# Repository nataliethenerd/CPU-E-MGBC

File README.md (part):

# Game Boy Pocket Color CPU E ONLY

Just incase you havent read it already, this is CPU E ONLY!!!!! CGB CPU E!

This board was adapted to CPU E by me, Natalie the Nerd. 
The CGB CPU E has a different pinout to the other varients of the CGB CPUs, I have documented the pinout via the board scans I created [here](https://github.com/nataliethenerd/boardscans/tree/main/CGB-CPU-06)

As a KiCad user, these boards were ported from Bucket Mouse's original Eagle files to KiCad using KiCad's built in converter. I cleaned them up and added the changes.

### MGBC CPU differences

The only differences is there is an added 2.5V LDO (NCP161ASN250T1G) and a couple more capacitors and no RAM. Here's the [iBom](https://nataliethenerd.github.io/mgbc-cpue.html)

Now onto the Mouse's original excellent documentation 

# Game Boy Pocket Color

My <a href="https://github.com/MouseBiteLabs/Game-Boy-DMG-Color">DMGC project</a> put a Game Boy Color put into an original Game Boy shell. But then I said, "Hey! This is neat, but I would rather it be small and cramped and have shorter battery life!" Enter the MGBC, or Pocket Color - a Game Boy Pocket (model name MGB) with the guts of a Game Boy Color (GBC). The PCB here is an original creation with some new features, though the concept and implementation of the "MGBC" or "Pocket Color" has been around for a while! Here are the project goals:

- A Game Boy Pocket aesthetic, using the original Game Boy Pocket shell and interfaces (link port, volume wheel, power switch, etc.), but with the capability of playing both Game Boy and Game Boy Color games.
- A nice, large IPS screen – the GBC Q5 XL IPS Backlight with OSD kit – with brightness and color palette control via the "navigation switch" housed where the contrast wheel used to be. (I will refer to the PCB attached to the Q5 screen as the “Q5 board”)
- A modernized, efficient switch mode power supply that can run off 2x AAA batteries or input from the DC jack, just like the original MGB. Testing shows that playing with NiMH AAA batteries can yield about 3.5 hours of gameplay at normal settings.
- Louder, cleaner sound through a modern audio amplifier.
- The option for tactile switches for the face buttons - like the GBA SP.
- No major externally viewable case modifications, to keep the OEM look and feel, outside of the screen, as much as possible.

All gerbers and source files can be found in this repo, as this project is fully open source. These PCB files and notes about the board, including customizations **and some troubleshooting tips**, can be found in the <a href="https://github.com/MouseBiteLabs/Game-Boy-Pocket-Color/tree/main/MGBC%20PCB#cpu-pin-functions">PCB folder</a>. Technical documentation of the board can be found in the <a href="https://github.com/MouseBiteLabs/Game-Boy-Pocket-Color/tree/main/Technical">Technical folder</a>.

**Do you want to make one?** Then you NEED TO READ this entire page. Seriously. Before asking a question, please review the <a href="https://github.com/MouseBiteLabs/Game-Boy-Pocket-Color#frequently-asked-questions">FAQ</a> at the bottom of the README for answers to.... frequently asked questions. Please try to find your answer in this repository - 95% of the time someone asks me something it's answered here already.

## Disclaimer

Before I go any further, please read this VERY important disclaimer, **IN IT'S ENTIRETY,** if you are thinking about making this yourself. **Don't let this picture happen to you!**

I made this project first and foremost for my own purposes. Nearly all of the features I have included are things I personally wanted. I have tried my hardest to make the project modular, if others would like to improve or change things easily, and I have also tried very hard to make the design somewhat less prone to potential errors during assembly. But in the end, every decision I made was for what I wanted the final product to be, with my skill level in mind.

So if you choose to build this project yourself, be warned - this is a considerably advanced, and expensive build. You must be comfortable with the fact that you may lose or damage expensive components. You are 100% liable for any damage done to your property or yourself. I am not responsible for any damage or loss of property incurred while attempting this project, or after completion of the project - you alone accept all risk. If you're *at all* questioning wether or not you can successfully attempt this project, please first practice with the <a href="https://github.com/MouseBiteLabs/Pocket-Mouse-Power-Board">Pocket Mouse Power Board</a> - this requires no original Game Boy parts, and the total parts cost of the board is less than $10. And before you dismantle a Game Boy, solder the FFC connector on the top of the MGBC board to make sure you are comfortable with long rows of fine pitch pins, as it is the same pin pitch as the much more expensive and important CPU. **If you have any difficulty assembling either the power board or the FFC connector, I highly discourage attempting the rest of the build.**

Furthermore, while I am confident in this design, I cannot claim full compatibility with every system configuration. **Especially if you decide to add a lithium-ion battery.** And there may be latent issues that have yet to crop up. If you see anything I may have missed, or some dubious design choice, feel free to ask questions or comment as such - feedback is appreciated, corrections are welcome.

In summation: **DO NOT attempt this project if you are uncomfortable or inexperienced with detailed electronics troubleshooting, or are not proficient in soldering! This is in NO WAY a beginner's project. You will AT MINIMUM need to be proficient in <a href="https://youtu.be/5uiroWBkdFY?t=110">drag soldering</a> and <a href="https://youtu.be/X3Rc1s6EpSI">hot air reflowing</a>. If you have not gained proficiency in these soldering skills, DO NOT ATTEMPT THIS PROJECT. You accept all risks and costs associated to this build if you choose to attempt it.**

(These parts are *tiny*. Quarter for scale - do not install a quarter in your final build.)

## Bill of Materials (BOM)

There are a handful of categories for the parts you need for this build. Please review all of them! The total BOM cost will come out to anywhere between $100 and $200 (NOT including the cost of a donor Game Boy Color console!) depending on the options you choose, which OEM parts you re-use, and any potential deals you can get on certain parts. Note that with the exception of a few components from a donor Game Boy Color, *most* of the electronic parts are brand new.

### I. Circuit Boards
  
First and foremost, you will need two brand new circuit boards for this build:
- <a href="https://github.com/MouseBiteLabs/Game-Boy-Pocket-Color/tree/main/MGBC%20PCB#mgbc-mbl-01">the main MGBC circuit board</a>, and 
- a power supply board that fits in the U5 socket on the MGBC board (like my <a href="https://github.com/MouseBiteLabs/Pocket-Mouse-Power-Board">Pocket Mouse Power Board</a>)

Again, I sell <a href="https://mousebitelabs.etsy.com/listing/1459241814/game-boy-pocket-color-pcb-mgbc-mbl-01?utm_source=Copy&utm_medium=ListingManager&utm_campaign=Share&utm_term=so.lmsm&share_time=1694127166906">the MGBC board</a> and <a href="https://mousebitelabs.etsy.com/listing/1473483915/pocket-mouse-power-board?utm_source=Copy&utm_medium=ListingManager&utm_campaign=Share&utm_term=so.lmsm&share_time=1694127201480">my regulator board</a> on my Etsy store. You can alternatively use the files in the MGBC PCB folder to order it yourself. Please see the MGBC PCB folder for more info.

You can also use other power supply boards from other creators - check the <a href="https://github.com/MouseBiteLabs/Game-Boy-Pocket-Color#v-compatibility-with-other-mods">Compatibility</a> section below for more information. 

**I don't recommend using an original power board from a Game Boy!**

### Information on Older Revisions

The current revision is v2.1, but you may have an earlier board (if you bought one from me, rest assured it will work perfectly fine - most of the changes between for-sale revisions are inconsequential to the end user). The BOM has changed slightly for v1.6 and later boards, compared to previous revisions. Please view the Excel and/or .csv file above for BOM information (or contact me). Here's a short list of information about the older boards, and what is required/recommended when using them:

| Revision | Recommendations |
| ---- | ---------------------------------------------------------------------------------------------------------------------------- |
| v1.0 | You are a masochist. You're on your own for this one.                                                                        |
| v1.1 | Are you me? No? Then did you rob my house?                                                                                   |
| v1.2 | You're one of the beloved beta testers. You didn't build it yet? For shame. Contact me.                                      |
| v1.3 | These should be practice boards only.                                                                                        |
| v1.4 | Use tactile buttons. Minor shell trimming may be required for volume dial and rocker switch.                                 |
| v1.5 | Minor shell trimming may be required for volume dial and rocker switch.                                                      |
| v1.6 | No important differences compared to the latest revision, but check EM7 and DC/BT+ requirements!                             |
| v2.0 | No important differences compared to the latest revision.                                                                    |

### II. Brand New Electronic Parts

The MGBC board uses mostly all-new components. This is not a direct-transfer board. The master BOM with every electronic component required for the main MGBC circuit board is provided in the folder in Excel format. Note that some parts may be out of stock at the links provided, but many can be found at alternate other retailers online, or have a proper substitute. Here is a saved cart from Mouser that contains all the parts in the BOM Excel, including some duplicates: https://www.mouser.com/ProjectManager/ProjectDetail.aspx?AccessID=854e7f6cf9

*Note: This cart link is for v1.6, v2.0, and v2.1 boards. Please check out the BOM Excel or .csv file above for information about v1.5 and earlier.*

Double check to see if any parts are missing, and consider ordering multiples of some parts. Also, there are some parts you may want to remove (like the tactile switches). **If a part is backordered, or out of stock** - check the Excel file, or the BOM listed at the bottom of the MGBC PCB folder. There may be alternate part options listed. You can also check for stock at places like Digikey, Newark, or LCSC. And you can always use Octopart.com to help find in-stock parts at other websites. Please understand that I can't maintain the cart for every out-of-stock part, so please do some research :)

Also note, while I do recommend the board, this BOM does not include parts for the Pocket Mouse Power Board. <a href="https://github.com/MouseBiteLabs/Pocket-Mouse-Power-Board">Please review my github on that board</a> for more information if you wish to use it for your power supply!

### III. Game Boy Electronic Parts

*Despite this being a **Pocket** Color, you don't actually need a Game Boy Pocket. However, this project **does require** at minimum a Game Boy Color.*

There are a handful of parts that I have not located aftermarket substitutes for, and will therefore necessitate an original Game Boy console to salvage from. Please note that removing these parts is not a trivial task, and **requires advanced soldering and desoldering skills to be successful.**

The following parts are required from an original Game Boy Color console:

  -	U1 – CGB CPU (all revisions *except* REV E, which is *incompatible*)
  - X1 – 8.388 MHz crystal oscillator

The following parts are required from an original Game Boy Color **OR** Game Boy Pocket console:

  -	P1 – Cartridge connector
  -	P5 – Headphone jack

The following parts can be salvaged from a Game Boy Color, but newly manufactured commercial off-the-shelf options exist:

  - U2 – LH52256CVTXIZ (SRAM); alternate: https://mou.sr/3f8G0Mi
  - EM10 – input filter; alternate: https://mou.sr/3FiMvXw

The following parts can be salvaged from a Game Boy Color *or* Game Boy Pocket, but aftermarket options exist:

  -	VR1 – Volume dial
  -	SW1 – Power switch
  -	P3 – Link port
  -	P4 – DC jack

### IV. External Build Parts

The following is the high-level BOM - basically, the Game Boy part. Note that parts that deviate from the ones listed here (like different shell designs) might necessitate different fitment modifications, or end up being incompatible. Note that this list is not a comprehensive list of all the places you can get these parts. I encourage you to search around if you can't find what you want here. 

-	**Shell:** I generally recommend the Funnyplaying "IPS Ready" ones if you don't want to trim anything. If you don't use these, then you're on your own for how to prepare it - generally, you can follow guides for preparing a Pocket for an IPS screen kit.
    - RGRS: <a href="https://retrogamerepairshop.com/products/funnyplaying-game-boy-pocket-q5-ips-ready-shell-housing-no-cut?pr_prod_strat=copurchase&pr_rec_id=d8b0186ad&pr_rec_pid=6280907751596&pr_ref_pid=6115075391660&pr_seq=uniform">FunnyPlaying Game Boy Pocket IPS Backlight Ready Shell Housing No Cut</a>
    - FunnyPlaying: <a href="https://funnyplaying.com/collections/product/products/gbp-retro-pixel-ips-coustom-shell?variant=33054643060797">GBP RETRO PIXEL IPS CUSTOM SHELL</a>
-	**Screen Kit:** This is the important one. You need this specific type of kit - the Q5 IPS with OSD. It goes by many names, the maker is Hispeedido (*not* FunnyPlaying). Kits that have the screen laminated to a GBC lens are *not* compatible, but kits that include a lit-up logo on the bottom part of the screen are fine to use. Make sure you DO NOT get the Game Boy Pocket version - it is not compatible! Also, be sure to test this screen kit before installing it, preferrably with an original Game Boy Color. Sometimes they arrive damaged, and once you've installed, it may not be possible to get a refund.
    - RGRS: <a href="https://retrogamerepairshop.com/products/game-boy-color-q5-ips-backlight-with-osd?variant=37646279213228">GBC Q5 XL IPS Backlight with OSD</a> OR <a href="https://retrogamerepairshop.com/collections/gbc-displays/products/game-boy-color-q5-osd-ips-kit-with-color-changing-logo?variant=41819042185388">Game Boy Color Q5 OSD IPS Kit with Color Changing Logo 
    - AliExpress: <a href="https://www.aliexpress.us/item/3256801650459088.html?spm=a2g0o.productlist.main.1.758e53f17WUFK2&algo_pvid=24ef67e3-d608-4269-a663-05eafed1bd17&algo_exp_id=24ef67e3-d608-4269-a663-05eafed1bd17-0&pdp_npi=3%40dis%21USD%2145.9%2145.9%21%21%21%21%21%4021224e9b16816641208271256d074d%2112000017802039303%21sea%21US%210&curPageLogUid=dCymHIE0cr4X">GBC Q5 IPS LCD Kit</a>
    - HHL: <a href="https://handheldlegend.com/products/game-boy-color-ips-lcd-q5-hispeedido">Game Boy Color IPS LCD Q5 - Hispeedido</a>
I have not thoroughly tested it, but the CGS (Cloud Game Store) display should be electrically compatible as of v2.0. It will need some kind of method of centering the image if you choose to use it, though. (At the time of writing, I have heard there is a seller on Taobao selling laminated CGS kits...)
  -	**Lens:** I recommend you get an "IPS Lens" as the viewing area is slightly larger than the OEM one. 
    - RGRS: <a href="https://retrogamerepairshop.com/collections/gbp-lenses-1/products/funnyplaying-game-boy-pocket-ips-retro-pixel-mod-led-hole-glass-screen-lens?variant=37635319988396">FunnyPlaying Game Boy Pocket IPS Retro Pixel Mod LED Hole Glass Screen Lens</a>
    - FunnyPlaying: <a href="https://funnyplaying.com/products/gbp-retro-pixel-ips-glass-lens?_pos=1&_sid=ec7345577&_ss=r&variant=31969857437757">GBP RETRO PIXEL IPS GLASS LENS</a>
- **Buttons:** Funnyplaying models are generally OEM-like (IMO), but you can also use OEM ones. Or any other maker of buttons! (Make sure you get Game Boy *Pocket* buttons - Game Boy *Color* buttons will not fit.)
  - RGRS: <a href="https://retrogamerepairshop.com/collections/gbp-buttons-1/products/funnyplaying-game-boy-custom-pocket-buttons?variant=41432879169708">FunnyPlaying Game Boy Pocket Custom Buttons</a>
  - LabFifteen: <a href="https://labfifteenco.com/collections/game-boy-pocket-buttons">Custom buttons</a>
  - FunnyPlaying: <a href="https://funnyplaying.com/products/gbp-custom-buttons?_pos=2&_sid=1bdf0ccb6&_ss=r&variant=33054652039229">GBP CUSTOM BUTTONS</a>
- **Membranes:** Important, but very forgettable! You will need them even if you install tactile switches.
  - RGRS: <a href="https://retrogamerepairshop.com/collections/gbp-buttons-1/products/funnyplaying-game-boy-pocket-silicone-button-contact-pad-membranes?variant=40593166401708">FunnyPlaying Game Boy Pocket Silicone Button Contact Pad Membranes
  - FunnyPlaying: <a href="https://funnyplaying.com/products/replacement-silicone-pads-for-gbp-mgb?_pos=3&_sid=1bdf0ccb6&_ss=r&variant=39378004705341">GBP/MGB REPLACEMENT SILICONE PADS</a>
- **Speaker:** There are tons of options for this as well, including using the OEM one. Game Boy Color *and* Game Boy Pocket speakers are compatible, since they are the same part.
  - RGRS: <a href="https://retrogamerepairshop.com/collections/gbp-audio/products/funnyplaying-clear-game-boy-color-speaker?variant=37728953761964">FunnyPlaying Clear Game Boy Color & Pocket Speaker</a>
  - FunnyPlaying: <a href="https://funnyplaying.com/products/clear-gbc-mgb-speaker?_pos=1&_sid=2cc6157b6&_ss=r">CLEAR GBC/MGB SPEAKER</a>
- **Battery Tabs:** This one is another part I commonly forget about. You *cannot* use Game Boy Color ones, you *must* use Game Boy Pocket battery terminals. Luckily, they're very easy to find.
  - RGRS: <a href="https://retrogamerepairshop.com/collections/gbp-power/products/gbp-game-boy-pocket-high-quality-replacement-battery-contact-terminals?variant=37893131305132">GBP Game Boy Pocket High Quality Replacement Battery Contact Terminals
- **Stickers:** Completely optional, but they can really bring a build together. Especially if you have custom Pocket Color stickers!
  - Nextstopplease: <a href="https://nextstopplease.square.site/product/gb-pocket-color-label/196?cp=true&sa=true&sbp=false&q=false">GB Pocket Color Label</a>
  - 8bitlabels: <a href="https://www.etsy.com/shop/8bitlabels?ref=simple-shop-header-name&listing_id=1097537372">8bitlabels on Etsy</a>

<b>Buying from RGRS? Consider helping out some cool people with these referral links:</b>
- <a href="https://retrogamerepairshop.com/?ref=ltyD2rUX">CodyWick</a>
- <a href="https://retrogamerepairshop.com/?ref=HSj4v5OO">JackV</a>

<b>Or use one of these other discount codes at checkout:</b>
- Nataliethenerd
- B23N
- Tito

### V. Battery Selection

I developed this system almost exclusively with rechargeable eneloop Pro NiMH AAA batteries. After finishing up development, I tried out regular alkaline AAAs. What I found, and some others have found, is that they are less reliable to use than NiMH batteries, particularly during start-up. When using alkaline batteries, after they have been discharged for an hour or two, sometimes the screen and power LED will flicker for a bit before fully coming on. This also varies between brands - I found Energizer Max batteries to perform much better than Duracell Coppertop batteries, for example. Duracells caused much more stuttering during the start-up sequence. Other brands or types may perform better, but I'm not about to buy a bunch of disposable alkalines to find out which.

However, the rechargeable NiMH AAA batteries I tested *do not* have any of these issues. And I tested these a lot during development, at many different states of charge. They are seemingly better suited for power delivery, and I never experience any kind of stuttering during start-up. I believe this is due to the generally higher internal resistance of alkaline batteries (a quick sampling of popular battery brands show approximately 50 mOhms internal resistance for NiMH chemistry, but 150+ mOhms internal resistance for alkaline chemistry). 

Rechargeable NiMH batteries give you about 3 to 6 hours of gameplay based on your settings and game selection, and as long as you have more than one set, you can easily charge one set while you play with another set. <A href="https://www.amazon.com/Panasonic-BK-4HCCA8BA-eneloop-Pre-Charged-Rechargeable/dp/B00JHKSL0A/ref=sr_1_1_pp?keywords=eneloop%2BAAA&qid=1690853200&sr=8-1&th=1">Here's a listing for the eneloop pro batteries I use in all of my Game Boys.</a> Other brands of rechargeable batteries I have seen used are Ikea LADDA batteries, and Jugee batteries.

#### Lithium Ion Batteries

Lithium-ion batteries (or LiPos) are another option, but I do not fully detail how to use them in this repository. You must be knowledgeable enough on your own to utilize them. Please review the entire repo for crucial information if you *do* decide to go with a LiPo.

I have created <a href="https://github.com/MouseBiteLabs/Pocket-Protector-Power-Board">my own LiPo board</a> to fit in the U5 socket, but I really recommend using AAAs. It will make the assembly easier and safer.

Nataliethenerd's <a href="https://www.nataliethenerd.com/product-page/safer-charge-dc">Safer Charge DC</a> board is also compatible with the MGBC. Instructions for how to use it is in the Testing and Assembly section.
  
### VI. Compatibility with Other Mods

You don't need any extra mods to complete the MGBC build, but there are some options available. One of the goals for the MGBC was to provide compatibility with various mods by other makers. In general, I tried to make the board similar to the Game Boy Pocket PCB in terms of solder points for different kinds of mods. The MGBC will not benefit from any mods that include audio amplification/"cleaning" or tactile button mods, as I've included those improvements already. Check out the <a href="https://github.com/MouseBiteLabs/Game-Boy-Pocket-Color/tree/main/MGBC%20PCB#customization-options">Customization Options</a> section in the MGBC PCB folder for information on those.
  
Here are a sample of my favorite mods for the MGBC:

  - <a href="https://www.etsy.com/listing/1348046388/game-boy-pocket-battery-indicator-mod">Leggomyfroggo's Two-Stage Battery Indicator Mod</a>: goes in place of the power LED, changes color when battery gets low
  - <a href="https://www.etsy.com/listing/1422095615/frogulator-game-boy-colorpocket-dc">Leggomyfroggo's Frogulator</a>: a power supply that slots into the U5 socket; eyes light up for battery power indication
  - <a href="https://www.muramasaentertainment.com/product/pocket-power-pocket/">Muramasa's Pocket-Power Pocket</a>: an all-in-one LiPo charger including USB-C port; requires some shell cuts and **removal of EM7 for v1.6 and earlier** [untested]
  - <a href="https://github.com/marshallh/gbpp">marshallh's Game Boy Pocket Power</a>: a power supply that slots into the U5 socket; has LiPo support (solder wires through the DC and BT+ holes on the MGBC board, and **remove EM7 on v1.6 and earlier** - requires USB-C board for charging and some shell cuts [untested]
  - <a href="https://github.com/skimzor/SZ-REG">skimzor's SZ Regulator</a>: a power supply that slots into the U5 socket; customizable print on the front of the board through <a href="https://ko-fi.com/skimzor">skimzor's Ko-Fi page</a>
  - <a href="https://www.nataliethenerd.com/product-page/gbp-led-boards">Natalie the Nerd's LED Boards</a>: button LED backlight board

Important note for using external mods: you must be aware that the voltage on the SW net (the output of the power switch, connected to pin 1 on the power board socket) will remain connected to the batteries as long as the power switch is on. If your mod connects to the power switch output, then be aware there *will* be a condition where the 5 V on-board is at zero volts, and the battery voltage will still be above 2 V. This may cause issues, such as power draw through resistors even when the power is off, or leakage through protection diodes in certain devices. Please use accordingly.

## Testing and Assembly

I'm going to split this into a few separate sections. This is the general process I follow when assembling an MGBC.

### Circuit Board Assembly

Usually when I'm populating a board, I follow this order:
  
1) Assemble all the non-Gameboy surface mount components first, not including P2, U2, C24, C29, and C45. 
  
2) After soldering these components, I solder the CPU and RAM in, then the FFC connector.
  
3) I use hot air and solder paste to reflow X1, C24, C29, and C45 onto the board. Be sure to either cover the FFC connector with kapton tape to avoid melting the plastic, or heat the board from the bottom.
 
If the build is going to utilize tactile buttons (the ones that are clicky, like on the GBA SP) I install *at least* the start and select ones now. After the headphone jack and DC jack are in, it's tricky to get the start and select tactiles in.
  
4) Finally, I add most of the other external-facing components - VR1, P3, P4, P5, SW1, SW2, D2, the speaker, and the battery terminals. The only parts that I don't populate at this point are the cartridge connector (P1) and the power board (U5). 

**NOTE 1** - Keep VR1 and SW2 as far inside the board as the holes allow. This will reduce interference with the shell. You may need to file away a bit of the shell in order for the knobs to turn freely. It may be a good idea to do a quick fitment test in the shell before going farther into assembly.

**NOTE 2** - You may have to trim the pins on VR1, the volume dial, before soldering. I cut them down in half to make them fit nicer.

### Setting up for AAA vs LiPo

I generally recommend using NiMH AAAs in builds, because they are easier and safer to deal with, they can be swapped in quickly as opposed to waiting for the battery to charge up, and don't require any shell modifications to use (LiPos require a shell cut to fit a USB port, which isn't fun). The only thing you need to do if you're going to use AAAs, which the MGBC is set up for natively, is connect the two holes labelled BT+ and DC together with a wire or 0 ohm resistor. This is also only required on v2.0 and later boards - v1.6 and earlier do not require this. Shorting these holes together connects the DC jack to the input of the regulator. So if you forget to add it, then your DC jack won't work (which may or may not matter to you anyway). **DO NOT SHORT THESE TOGETHER IF USING A LITHIUM-ION BATTERY.**

If you really want to add LiPo support to your build, you're on your own for figuring out how to set it up. The important thing to note on the MGBC board is, for boards v1.6 and earlier, **DO NOT INCLDE EM7**. This component must be removed from the final build. Make absolutely sure you do this - failure to do so may damage your battery and/or system. In version 2.0, you must include EM7 on every build.

Also, to get the power LED to dim at the correct time, remove R6 from the main MGBC board.

If you're using Nataliethenerd's <a href="https://www.nataliethenerd.com/product-page/safer-charge-dc">Safer Charge DC</a>, connect a wire from the "To F1" pad on the back of the board to the BT+ hole on the MGBC, and a wire from the "To 5V" pad on the back of the board to the pad on the USB-C breakout board. Then install the board into the U5 socket as normal.

And, as a mandatory disclaimer, **LITHIUM-ION BATTERIES ARE DANGEROUS. USE AT YOUR OWN RISK. I AM NOT RESPONSIBLE FOR YOUR HOUSE BURNING DOWN. YOU ARE RESPONSIBLE FOR FIGURING OUT HOW TO USE A LIPO ON THIS BOARD.**

### Testing the Power Board and IPS Kit
  
The next step to test is the power board, or U5. If you are using my LiPo power board, the steps to test that board are detailed <a href="https://github.com/MouseBiteLabs/Pocket-Protector-Power-Board">in the repository.</a> I *highly* suggest making sure you've assembled the power board correctly before directly connecting it and powering it all on, cowboy style. If you're able to test your power board before installation, definitely do that, but if you're not sure how, or don't have the ability, then you can actually use your mostly-assembled MGBC board to test it. 
  
Solder wires on pins 1, 2, and 3 from the MGBC board to the power board (the left three holes of the power board). Don't connect the other side of four pins just yet - pin 7 is the 5 V pin, which powers the rest of the Game Boy. Keeping pin 7 depopulated, you can place the Game Boy in the back half of the shell to connect up batteries, or use a power supply clipped to the battery terminals. Turn the power switch on. Use a multimeter to measure the voltage from pin 7 (positive test probe) to GND (negative test probe). You should read approximately 5 V here - anything more than 5.1 V or less than 4.9 V means you've likely got something wrong on your power board.
  
(In this picture, the red circle is pin 7, the blue circle is pin 3, or GND - this is for illustrative purposes only, I recommend testing the board before fully mounting it to the MGBC board.)

If you confirm you have 5 V on pin 7, then remove the wires and connect the board via header pins (if not, check the next section for some troubleshooting advice). Finally, you'll want to test the screen kit. Slide the FFC cable into P2 on the MGBC board, and make sure the cable is all the way in and the bale is pushed all the way down. Let the screen hang over the front of the board. I recommend placing something insulative - like a piece of paper, or kapton tape - over the empty holes of the cart connector, to prevent the back of the display from shorting on the pins. If you have a power supply, you can use that to power it on the battery terminals (set it for 3 V, 1.5 A). If not, you can again put the Game Boy in the back half of a Game Boy Pocket shell to use batteries. (I have mixed results with using battery holders with alligator clips.)

Turn it on, and check for these things:
  
1) Power LED turns on
2) The speaker makes the start-up ding (use headphones to check both left and right channels, and check the volume)
3) The screen shows the GBC splash logo
  
Some quick troubleshooting tips - first, make sure the batteries are in all the way (or your power supply is set correctly) and the cable for the IPS kit is inserted fully and the bale is pushed all the way down. If only the LED isn't turning on, you might have the LED backwards. If you can hear the start-up noise, but nothing on the screen, then check the connections on the FFC connector and the top row of pins on the CPU - they probably need a reflow. If you get a blank screen, but no start-up jingle, then check the connections on the FFC, CPU, and RAM chips. And if you have the splash screen, but no audio, then check your speaker, headphone jack, and orientation of tantalum capacitors. If nothing is happening when you flip the switch, or you still cant figure out where your error is coming from, check out the <a href="https://github.com/MouseBiteLabs/Game-Boy-Pocket-Color#troubleshooting-common-electrical-issues">Troubleshooting</a> section for a few more detailed troubleshooting tips, and the <a href="https://github.com/MouseBiteLabs/Game-Boy-Pocket-Color/tree/main/MGBC%20PCB#cpu-pin-functions">CPU Pin Function diagram</a> in the PCB folder.

*Note: If you're using the Pocket Mouse Power Board, you may have to wait a few seconds after inserting batteries the first time before it will turn on with the power switch. Once the batteries have been in the system for a few seconds, it will act completely normally.*
  
Once you've verified the system boots up correctly, and you have acceptable sound coming out of the speakers and headphones with the start-up noise, you can go ahead and put the cart connector into the board. I save this for last, because there are a few components in the audio circuit close to the connector, and they're difficult to rework without melting the cart connector plastic.
  
When you install the cartridge connector, be sure to trim down the pins nearly flush to the PCB. Then, I usually cover the exposed solder with kapton tape. The Q5 screen sits right above these pins, and the back of it can short to the cart connector pins once the system is fully assembled.

You will also want to test out the cartridge connector! Put the screen back in, and power it up like you tested above, but with a game inserted this time. If you get a garbled Nintendo logo, or the game doesn't boot at all, make sure your cartridge and cartridge connector are cleaned. You may also want to reflow the cart connector or the bottom row of CPU pins in case one of those lines are not making proper connection.

I suggest running the color tests in the <a href="https://github.com/pinobatch/240p-test-mini/releases/">240p test suite ROM</a>, if you have a flash cart to run it on. It will tell you if you have any poor connections on the FFC lines - the screen might work, but you might be missing a connection on one of the 15 RGB pins! If your colors look off, reflow the connections on the top row of pins on the CPU and/or the FFC connector. This picture (provided by <a href="https://retrogamerepairshop.com/?ref=HSj4v5OO">JackV</a>) shows a before and after pic for reflowing a few mis-soldered color pins.

### Customization Options

There are a number of options you have to customize your build. This includes, among other things: adding a reset button, adding tactile switches for the buttons, and changing the brightness of the LED. Review the <a href="https://github.com/MouseBiteLabs/Game-Boy-Pocket-Color/tree/main/MGBC%20PCB#customization-options">Customization Options</a> section of the MGBC PCB folder for more information.

This is also the point where I would install any desired mods discussed above in the <a href="https://github.com/MouseBiteLabs/Game-Boy-Pocket-Color#v-compatibility-with-other-mods">Mod Compatibility</a> section (other than power boards, obviously). Though, there aren't too many mods out there that would be required to add. Again, there is absolutely no need for additional audio mods or power cleaner mods on this build.

### Troubleshooting Common Electrical Issues

I'm not going to delve into a lot of detail here, just some basic troubleshooting you can perform. Remember, this project is meant for those with experience in electronics assembly and troubleshooting, so you should be able to figure some of this out by yourself! These tips won't include simple things to check like "check for cold solder joints" or "make sure you have the right parts installed" and whatnot, but that doesn't mean that isn't your root cause!

**Issue: No power to U5 pins 1 or 2**

Are you getting voltage out of the batteries or DC jack? Measure the voltage across pin 2 of the U5 socket to GND - this should read whatever voltage your batteries or DC jack is outputting. Measuring the voltage from pin 1 of U5 to GND will give you the same result as pin 2 when the power switch is on, or zero volts when the power switch is off. 

If you get incorrect results, then check the following:
  - Make sure F1 or F2 are not blown. (Were you soldering when you had batteries installed? For shame!)
  - Check orientation of D1 - did you put it in backwards?
  - Check orientation of EM10 - is it 90 degrees rotated?
  - Check for a dirty DC jack (P4) - you should read nearly zero ohms with a resistance check across pins 2 and 3 when you don't have anything plugged in!
  - Make sure the batteries completely touch the battery terminals in the battery bay. This frequently happens to me in aftermarket shells without the battery separator.
  - Clean your power switch regardless of any issues (it will improve the switch action reliability), but if it's particularly dirty, you may not get any voltage reading on pin 1 even when it's turned on
  
**Issue: Severe power glitches during start-up; plugging in headphones sometimes resets system**
  
  - Make sure C8, C21, C26, and C27 are placed in the correct orientation. Remember, the stripe on tantalum capacitors indicates the POSITIVE side of the device.
  - Ensure R22/R23 are 1 kΩ resistors.
  - Clean your power switch properly.
  
**Issue: No sound or bad quality sound**

- Make sure C8, C21, C26, and C27 are placed in the correct orientation.
- Plug in headphones to check if the issue is related to the speaker or both speaker and headphones. If you get audio out of your headphones but not your speaker, then:
  - Check for continuity from pin 5 on the headphone jack (top right corner when viewing from below) to GND. When headphones are not plugged in, this pin should be connected to ground. If it isn't, clean your headphone jack, or get another.
  - Try another speaker, if you have one.
- If your issue is both speaker *AND* headphones, then:
  - Clean your volume dial by dripping IPA in it and spinning it back and forth. Consider replacing it with a new aftermarket version.
  - Reflow components in the audio circuit and/or the CPU audio pins.
  
**Issue: White screen, glitchy display, miscolored display, stuck on the boot logo**

- Make sure your screen ribbon cable is inserted all the way into P2 and the bale is pushed all the way down.
- Reflow the SRAM (U2) and make sure all pins are well-connected to the board.
- Reflow the FFC connector (P2) and make sure all pins are well-connected to the board.
- Reflow the CPU (U1) and make sure all pins are well-connected to the board.
- If miscolored, make sure the palette isn't being cycled on the IPS kit, as there is a touchpad that cycles through different color modes.
- If you're stuck on the boot screen *only* with a game inserted, check to make sure the cartridge and cartridge connector you're using is clean and making good contact.

### Final Assembly

Before assembling the board into the shell, it's a good idea to prepare the Q5 board solder pads. First, remove the touch sensor leads. Then cut six 30 gauge wire segments and solder them on the brightness, palette, battery, and OSD input pads. You do not need to solder a wire to the GND pad. The one connected to the brightness touch sensor pad will be longer than the others, as it has to cut over to the other side of the board. These wires will be soldered to the top of the board after the screen is installed.

Then, put the lens on the front half of the shell, take the screen protector off of the IPS screen, and carefully place it in the back half of the shell - be sure no dust or hair is between the lens and the screen! Then place the buttons and membranes down.

**Note: Be extremely careful with the screen. It is fragile. If you break it, you can sometimes buy one separately. They're just screens that were used in Blackberry Q5 phones.**
  
Next is to put the assembled PCB into the shell. Remember that you may need to lightly file away part of the shell around VR1 (volume dial) and/or SW2 (rocker switch) if the knobs interfere with the shell. Put screws down into the proper holes, and feed the IPS kit cable into P2 and secure the bale. The cable is a bit stiff so be careful installing it. Also at this point, *very carefully* solder the six wires from the IPS kit onto the main MGBC PCB. **Be extremely cautious not to melt any plastic on the shell!** Though if you're attempting this mod, I would hope you have a steady enough hand to keep the soldering iron away from the melty bits ;)

Then all that's left is to put the power switch in its holder, and secure the back half of the shell on. Well, and center the image. It's going to be offset a bit. That's where the Q5 kit's image-centering functionality comes into play. Open the menu by pressing Select, A, and B at the same time. Navigate up and down in the menu with A and B respectively, and hold select and press A to select the screen offset options (select+A again confirms your change, select+B backs out of it). Adjust the V (and maybe H) coordinates so that the image is centered, for my build this was about 46 vertical, 37 horizontal.

*Also, if your screen kit includes the option for a backlit Game Boy Color lens logo, be sure to disable that in the OSD menu. On the left picture you can see the blue bar at the bottom, that's the backlit logo option before disabling it.*

Add any stickers you want, and the MGBC is complete!

## Auxilliary Controls
### Q5 XL IPS Backlight with OSD
-	Select + A + B: Open the OSD menu
-	Select + A: Enter
-	Select + B: Exit
-	A: Increase
-	B: Decrease

### Navigation Switch
-	Rock up: Advance screen brightness setting
-	Rock up/Hold: Toggle on-screen battery indicator
-	Rock down: Advance screen color pallete setting
-	Rock down/Hold: Toggle on-screen pixel grid
-	Push in: System reset
  
## Power Draw Measurements
For these estimates, battery life was measured using two eneloop pro NiMH AAA batteries (total of ~2232 mWh) while playing the Legend of Zelda: Link's Awakening intro on loop. Keep in mind, these are rough estimates. I rounded to the nearest 5 minute interval, and the nearest 5 mW interval. Actual playtime *will* vary due to a variety of factors, but these should be good ballpark numbers. 

In general, you can expect to get between 3 and 6 hours of gameplay depending on the game, your play settings, and the batteries you're using. The power LED will dim with about 10 to 20 minutes left of playtime.

| IPS Screen Brightness | Cartridge Type | Volume | Headphones? | Playtime       | Power Draw (mW) |
| --------------------- | -------------- | ------ | ----------- | -------------- | --------------- |
| Max                   | Everdrive X5   | Max    | No          | 3 hrs, 15 mins | 680             |
| Max                   | Everdrive X5   | Max    | Yes         | 3 hrs, 30 mins | 635             |
| Max                   | Everdrive X5   | Min    | N/A         | 3 hrs, 30 mins | 630             |
| Max                   | OEM Cart       | Max    | No          | 3 hrs, 30 mins | 630             |
| Max                   | OEM Cart       | Max    | Yes         | 3 hrs, 45 mins | 590             |
| Max                   | OEM Cart       | Min    | N/A         | 3 hrs, 50 mins | 585             |
| Min                   | Everdrive X5   | Max    | No          | 4 hrs, 25 mins | 500             |
| Min                   | Everdrive X5   | Max    | Yes         | 4 hrs, 45 mins | 465             |
| Min                   | Everdrive X5   | Min    | N/A         | 4 hrs, 50 mins | 460             |
| Min                   | OEM Cart       | Max    | No          | 4 hrs, 50 mins | 460             |
| Min                   | OEM Cart       | Max    | Yes         | 5 hrs, 20 mins | 420             |
| Min                   | OEM Cart       | Min    | N/A         | 5 hrs, 25 mins | 415             |

The variable that affects battery life the most is the screen brightness. I have found that the power drop from full to half brightness is much larger than the drop from half to minimum brightness, so I recommend playing at half brightness to maximize playtime without sacrificing a vibrant screen. As for cart type, I only own an Everdrive X5, which of the flash cart offerings is one of the most power efficient. So something like the EZ Flash Jr. is likely to drain batteries even faster. 

The difference in power draw between max and min screen brightness is about 170 mW, between an OEM cart and an Everdrive X5 is about 45 mW, between max and min volume on speakers is about 45 mW, and between headphones and speakers is about 40 mW.

### Battery Discharge Curves

These are six curves generated from data used to populate the table above, with the x-axis being depth of discharge.

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
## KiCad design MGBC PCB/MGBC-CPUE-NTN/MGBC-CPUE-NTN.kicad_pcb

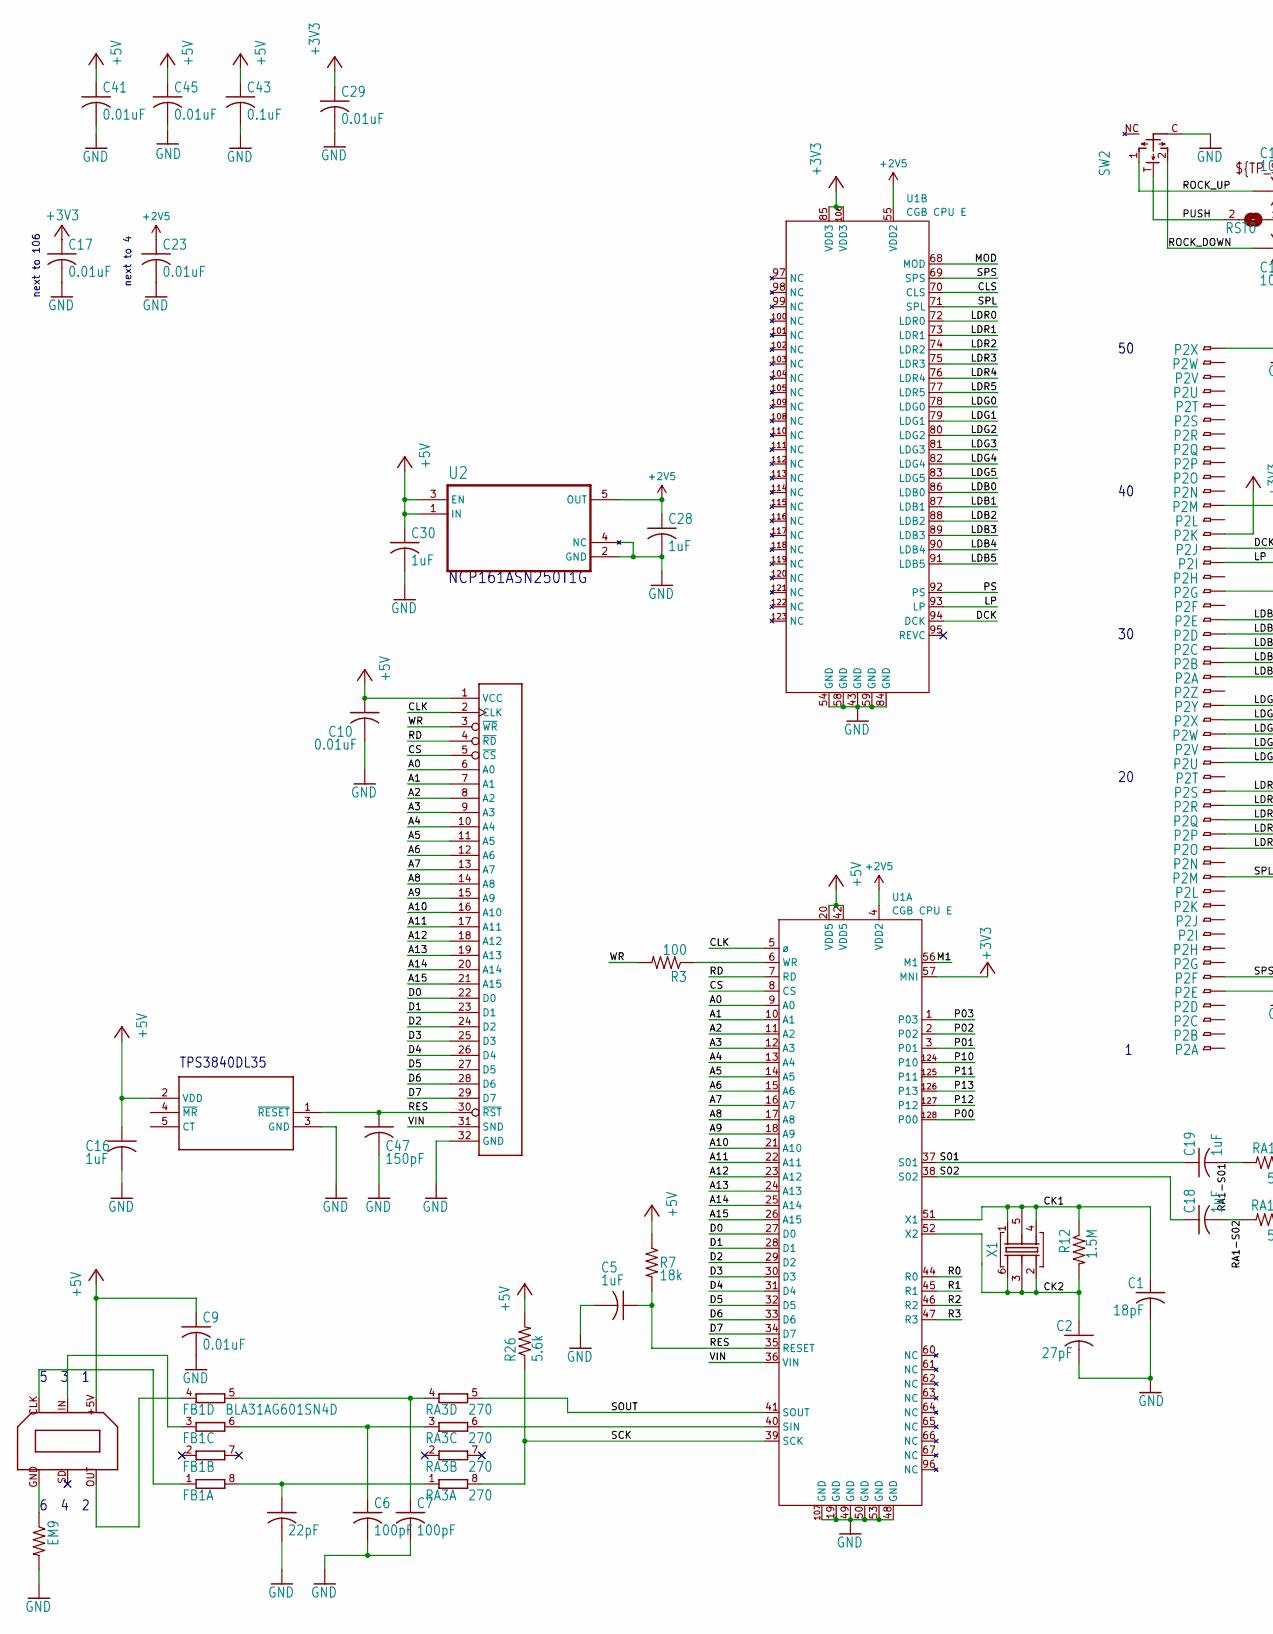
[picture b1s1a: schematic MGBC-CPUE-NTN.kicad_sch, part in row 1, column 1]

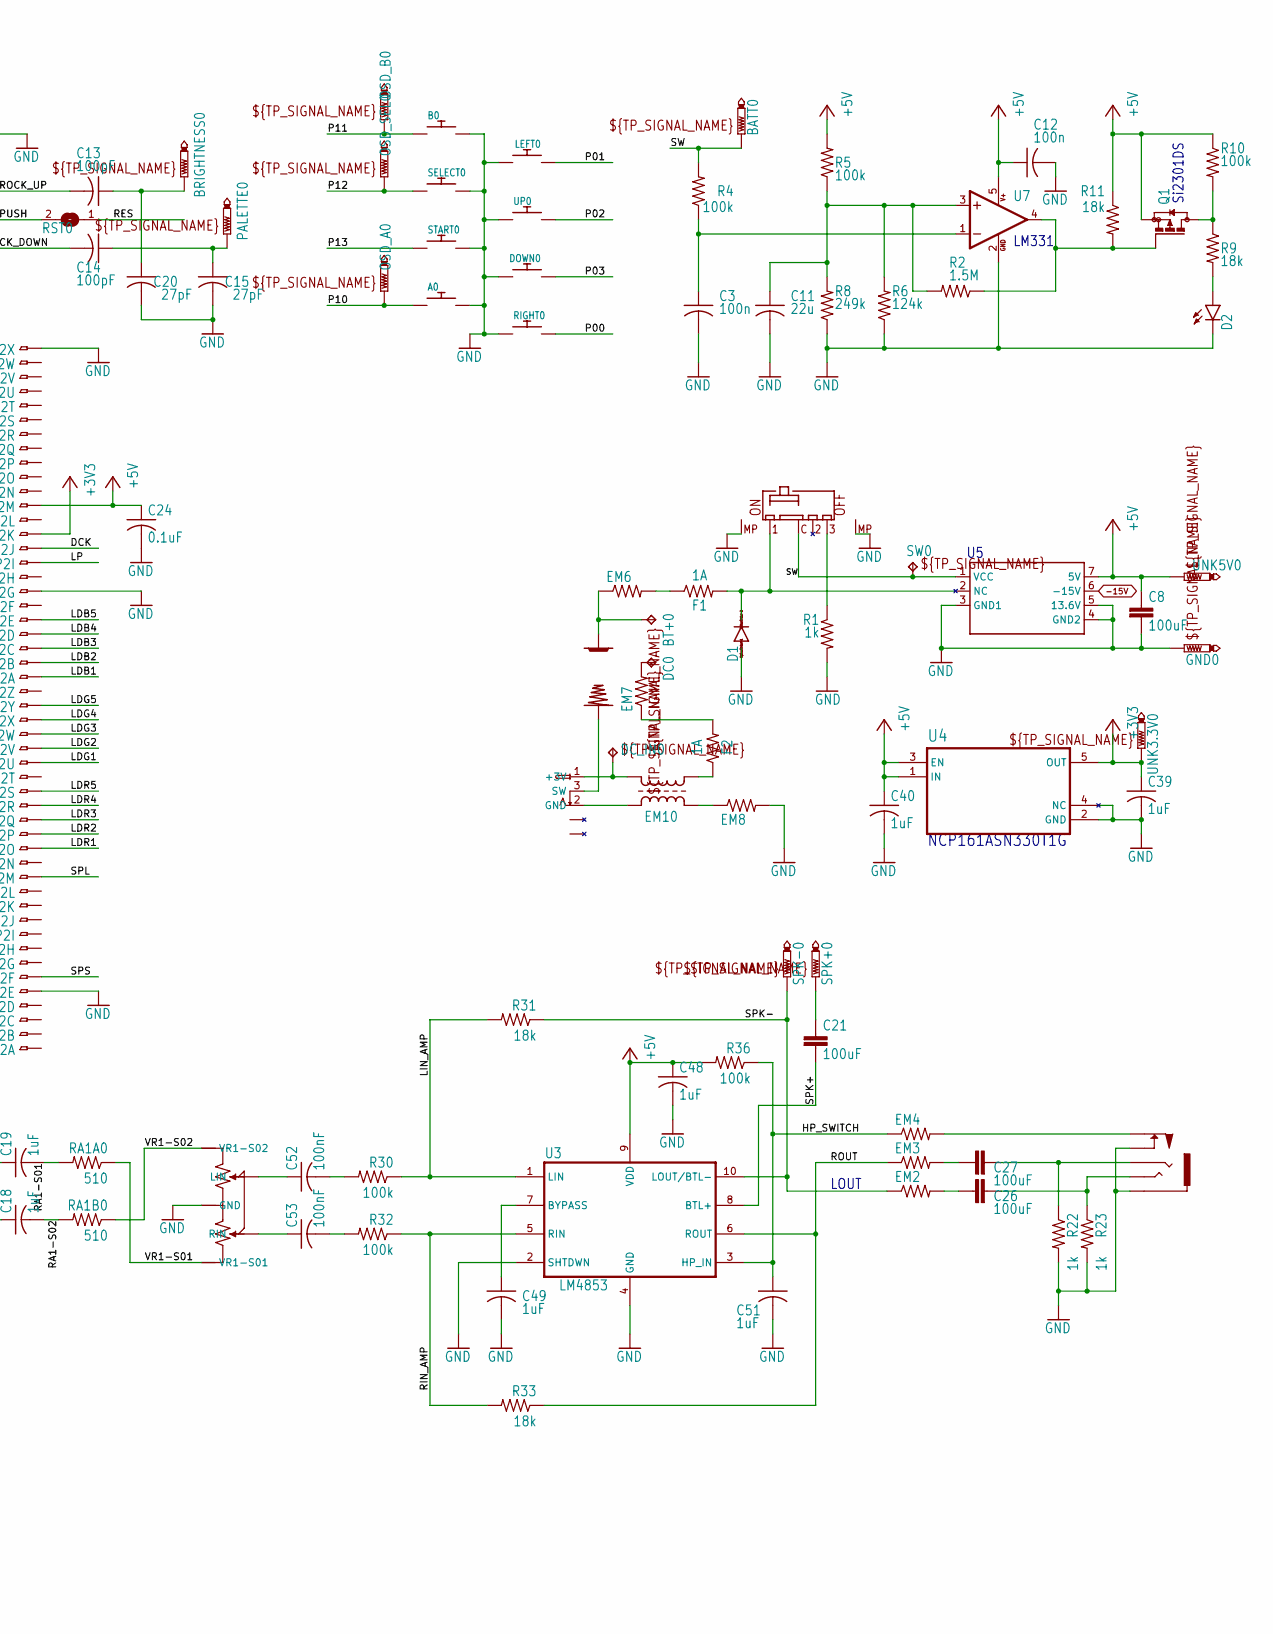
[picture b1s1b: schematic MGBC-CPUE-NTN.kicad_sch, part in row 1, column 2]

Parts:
+0: MGB+BATTERY4
-0: MGB-BATTERY4
A0: DMG-BTN; DMG_BTN3
B0: DMG-BTN; DMG_BTN3
BATT0: PTR1TP20R; TP20R
BRIGHTNESS0: PTR1TP20R; TP20R
BT+0: TPPAD1-13; P1-13
C1: 18pF; C0603
C2, C15, C20: 27pF; C0603
C3, C12: 100n; C0603
C4: 22pF; C0603
C5, C16, C18, C19, C28, C30, C39, C40, C48, C49, C51: 1uF; C0603
C6, C7, C13, C14: 100pF; C0603
C8, C21, C26, C27: 100uF; C1210
C9, C10, C17, C23, C29, C41, C45: 0.01uF; C0603
C11: 22u; C0805
C24, C43: 0.1uF; C0603
C47: 150pF; C0603
C52, C53: 100nF; C0603
D1: CGRM400-G; SOD-123_MINI-SMA
D2: LED3MM
DC0: TPPAD1-13; P1-13
DC_IN0: TPTP20R; TP20R
DOWN0: DMG-BTN; MGB_BTN_DPad
EM2, EM3, EM4, EM9: BLM18BD102SN1D; R0603
EM6, EM7, EM8: Z0805C221BPWZT; R0805
EM10: ACM4532-801-2PA; ACM4532
F1, F2: 1A; R0603
FB1: BLA31AG601SN4D; EXB38V
GND0: PTR1B1,27; B1,27
LEFT0: DMG-BTN; MGB_BTN_DPad
OSD_A0: PTR1TP20R; TP20R
OSD_B0: PTR1TP20R; TP20R
OSD_SEL0: PTR1TP20R; TP20R
P1: MGB-CART
P2: GBC_LCDH; 62684-502100AHLF
P3: LINKPORTCGB-LINK; CGB-LINK
P4: MGB-PWRJACK
P5: MGBHPMGB; MGB-HEADPHONE
PALETTE0: PTR1TP20R; TP20R
Q1: BSS84; SOT23
R1, R22, R23: 1k; R0603
R2, R12: 1.5M; R0603
R3: 100; R0603
R4, R5, R10, R30, R32, R36: 100k; R0603
R6: 124k; R0603
R7, R9, R11, R31, R33: 18k; R0603
R8: 249k; R0603
R26: 5.6k; R0603
RA1A0, RA1B0: 510; R0603
RA3: 270; EXB38V
RIGHT0: DMG-BTN; MGB_BTN_DPad
RST0: SJ
SELECT0: DMG-BTN; DMG_BTN1_W2
SPK+0: PTR1PAD1-13; P1-13
SPK-0: PTR1PAD1-13; P1-13
START0: DMG-BTN; DMG_BTN1_W2
SW0: TPTP20R; TP20R
SW1: MGB-SW1; MGB-SWITCH
SW2: NAV_SWITCH
U1: CGB CPU E; QFP-128
U2, U4: TLV70233QDBVRQ1; SOT95P280X145-5N
U3: LM4853; VSSOP10
U5: MGB-PWR_BD; MGB-PWRBD
U6: TPS3840; SOT-23-5
U7: TL331; DBV-R-PDSO-G5
UNK3.3V0, UNK5V0: PTR1B1,27; B1,27
UP0: DMG-BTN; MGB_BTN_DPad
VR1: MGB-POT""; MGB-POT
X1: 8.388608MHZ-4-PAD; 7.5X5-4-PAD

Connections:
+2V5: C23.1, C28.1, U1.4 (VDD2), U1.55 (VDD2), U2.5 (OUT)
+3V3: C17.1, C29.1, C39.1, P2.37 (1), U1.57 (MNI), U1.85 (VDD3), U1.106 (VDD3), U4.5 (OUT), UNK3.3V0.TP
+5V: C8.1, C9.1, C10.1, C12.1, C16.1, C24.1, C30.1, C40.1, C41.1, C43.1, C45.1, C48.1, P1.1 (VCC), P2.39 (1), P3.+5V, Q1.2 (S), R5.2, R7.1, R10.1, R11.1, R26.2, R36.2, U1.20 (VDD5), U1.42 (VDD5), U2.1 (IN), U2.3 (EN), U3.9 (VDD), U4.1 (IN), U4.3 (EN), U5.7 (5V), U6.2 (VDD), U7.5 (V+), UNK5V0.TP; also elsewhere on the board
-15V: U5.6 (-15V)
/A0: P1.6 (A0), U1.9 (A0)
/A1: P1.7 (A1), U1.10 (A1)
/A2: P1.8 (A2), U1.11 (A2)
/A3: P1.9 (A3), U1.12 (A3)
/A4: P1.10 (A4), U1.13 (A4)
/A5: P1.11 (A5), U1.14 (A5)
/A6: P1.12 (A6), U1.15 (A6)
/A7: P1.13 (A7), U1.16 (A7)
/A8: P1.14 (A8), U1.17 (A8)
/A9: P1.15 (A9), U1.18 (A9)
/A10: P1.16 (A10), U1.21 (A10)
/A11: P1.17 (A11), U1.22 (A11)
/A12: P1.18 (A12), U1.23 (A12)
/A13: P1.19 (A13), U1.24 (A13)
/A14: P1.20 (A14), U1.25 (A14)
/A15: P1.21 (A15), U1.26 (A15)
/CK1: C1.1, R12.1, U1.51 (X1), X1.1, X1.4, X1.5
/CK2: C2.1, R12.2, U1.52 (X2), X1.2, X1.3, X1.6
/CLK: P1.2 (CLK), U1.5 (ø)
/CLS: U1.70 (CLS)
/CS: P1.5 (~CS), U1.8 (CS)
/D0: P1.22 (D0), U1.27 (D0)
/D1: P1.23 (D1), U1.28 (D1)
/D2: P1.24 (D2), U1.29 (D2)
/D3: P1.25 (D3), U1.30 (D3)
/D4: P1.26 (D4), U1.31 (D4)
/D5: P1.27 (D5), U1.32 (D5)
/D6: P1.28 (D6), U1.33 (D6)
/D7: P1.29 (D7), U1.34 (D7)
/DCK: P2.36 (1), U1.94 (DCK)
/HP_SWITCH: C51.1, EM4.1, R36.1, U3.3 (HP_IN)
/LDB0: U1.86 (LDB0)
/LDB1: P2.27 (1), U1.87 (LDB1)
/LDB2: P2.28 (1), U1.88 (LDB2)
/LDB3: P2.29 (1), U1.89 (LDB3)
/LDB4: P2.30 (1), U1.90 (LDB4)
/LDB5: P2.31 (1), U1.91 (LDB5)
/LDG0: U1.78 (LDG0)
/LDG1: P2.21 (1), U1.79 (LDG1)
/LDG2: P2.22 (1), U1.80 (LDG2)
/LDG3: P2.23 (1), U1.81 (LDG3)
/LDG4: P2.24 (1), U1.82 (LDG4)
/LDG5: P2.25 (1), U1.83 (LDG5)
/LDR0: U1.72 (LDR0)
/LDR1: P2.15 (1), U1.73 (LDR1)
/LDR2: P2.16 (1), U1.74 (LDR2)
/LDR3: P2.17 (1), U1.75 (LDR3)
/LDR4: P2.18 (1), U1.76 (LDR4)
/LDR5: P2.19 (1), U1.77 (LDR5)
/LIN_AMP: R30.1, R31.2, U3.1 (LIN)
/LP: P2.35 (1), U1.93 (LP)
/M1: U1.56 (M1)
/MOD: U1.68 (MOD)
/P00: RIGHT0.2, U1.128 (P00)
/P01: LEFT0.1, U1.3 (P01)
/P02: U1.2, UP0.2
/P03: DOWN0.1, U1.1 (P03)
/P10: A0.1, OSD_A0.TP, U1.124 (P10)
/P11: B0.2, OSD_B0.TP, U1.125 (P11)
/P12: OSD_SEL0.TP, SELECT0.2, U1.127 (P12)
/P13: START0.2, U1.126 (P13)
/PS: U1.92 (PS)
/PUSH: RST0.2, SW2.T; also elsewhere on the board
/R0: U1.44 (R0)
/R1: U1.45 (R1)
/R2: U1.46 (R2)
/R3: U1.47 (R3)
/RA1-S01: C19.2, RA1A0.2
/RA1-S02: C18.2, RA1B0.2
/RD: P1.4 (~RD), U1.7 (RD)
/RES: C5.1, C47.1, P1.30 (~RST), R7.2, RST0.1, U1.35 (RESET), U6.1 (~RESET); also elsewhere on the board
/RIN_AMP: R32.1, R33.2, U3.5 (RIN)
/ROCK_DOWN: C14.2, SW2.2
/ROCK_UP: C13.2, SW2.1
/ROUT: EM3.1, R33.1, U3.6 (ROUT)
/S01: C19.1, U1.37 (S01)
/S02: C18.1, U1.38 (S02)
/SCK: R26.1, RA3.8 (2), U1.39 (SCK)
/SOUT: RA3.5 (2), U1.41 (SOUT)
/SPK+: C21.2, U3.8 (BTL+)
/SPK-: EM2.1, R31.1, SPK-0.TP, U3.10 (LOUT/BTL-)
/SPL: P2.13 (1), U1.71 (SPL)
/SPS: P2.6 (1), U1.69 (SPS)
/SW: BATT0.TP, R4.2, SW0.TP, SW1.P$C (C), U5.1 (VCC)
/VIN: P1.31 (SND), U1.36 (VIN)
/VR1-S01: RA1A0.1, VR1.P$5 (VR1-S01)
/VR1-S02: RA1B0.1, VR1.P$4 (VR1-S02)
/WR: P1.3 (~WR), R3.2
GND: A0.2, B0.1, C1.2, C2.2, C3.2, C4.2, C5.2, C6.2, C7.2, C8.2, C9.2, C10.2, C11.2, C12.2, C15.2, C16.2, C17.2, C20.2, C23.2, C24.2, C28.2, C29.2, C30.2, C39.2, C40.2, C41.2, C43.2, C45.2, C47.2, C48.2, C49.2, C51.2, D1.A, D2.K (C), DOWN0.2, EM8.2, EM9.2, GND0.TP, LEFT0.2, P1.32 (GND), P2.5 (1), P2.33 (1), P2.50 (1), P3.P$10 (GND), P5.GND (S), P5.SWGND (SWB), R1.2, R6.1, R8.1, R22.2, R23.2, RIGHT0.1, SELECT0.1, START0.1, SW1.P$MP1 (MP1), SW1.P$MP2 (MP2), SW2.C, U1.19 (GND), U1.43 (GND), U1.48 (GND), U1.49 (GND), U1.50 (GND), U1.53 (GND), U1.54 (GND), U1.58 (GND), U1.59 (GND), U1.84 (GND), U1.107 (GND), U2.2 (GND), U2.4 (NC), U3.2 (SHTDWN), U3.4 (GND), U4.2 (GND), U4.4 (NC), U5.3 (GND1), U5.4 (GND2), U5.5 (13.6V), U6.3 (GND), U7.2 (GND), UP0.1, VR1.P$1 (GND); also elsewhere on the board
unnamed: +0.P$1, +0.P$2, +0.P$3, BT+0.TP, EM6.1
unnamed: BRIGHTNESS0.TP, C13.1, C20.1
unnamed: C14.1, C15.1, PALETTE0.TP
unnamed: C21.1, SPK+0.TP
unnamed: C26.1, EM2.2
unnamed: C27.1, EM3.2
unnamed: C27.2, P5.R, R22.1
unnamed: C52.2, R30.2
unnamed: C53.2, R32.2
unnamed: D2.A, R9.2
unnamed: DC0.TP, EM7.2
unnamed: EM6.2, F1.1
unnamed: EM7.1, F2.2
unnamed: EM9.1, P3.GND
unnamed: EM10.1, F2.1
unnamed: EM8.1, EM10.2
unnamed: FB1.1, P3.CLK
unnamed: C4.1, FB1.8 (2), RA3.1
unnamed: FB1.3 (1), P3.IN
unnamed: C6.1, FB1.6 (2), RA3.3 (1)
unnamed: FB1.4 (1), P3.OUT
unnamed: C7.1, FB1.5 (2), RA3.4 (1)
unnamed: DC_IN0.TP, EM10.4, P4.1 (+3V)
unnamed: EM10.3, P4.2 (GND)
unnamed: -0.P$1, -0.P$3, -0.P$4, P4.3 (SW)
unnamed: EM4.2, P5.SW (SWA)
unnamed: C26.2, P5.L (T), R23.1
unnamed: Q1.3 (D), R9.1, R10.2
unnamed: Q1.1 (G), R2.1, R11.2, U7.4 (OUT)
unnamed: RA3.6 (2), U1.40 (SIN)
unnamed: D1.C, F1.2, SW1.P$1 (1), U5.2 (NC)
unnamed: R1.1, SW1.P$3 (3)
unnamed: R3.1, U1.6 (WR)
unnamed: C49.1, U3.7 (BYPASS)
unnamed: C11.1, R2.2, R5.1, R6.2, R8.2, U7.3 (+IN)
unnamed: C3.1, R4.1, U7.1 (-IN)
unnamed: C52.1, VR1.P$3 (LIN)
unnamed: C53.1, VR1.P$2 (RIN)

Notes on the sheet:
6 4 2
next to 4
next to 106
Si2301DS
NCP161ASN330T1G
TPS3840DL35
5 3 1
LM331
NCP161ASN250T1G
LOUT

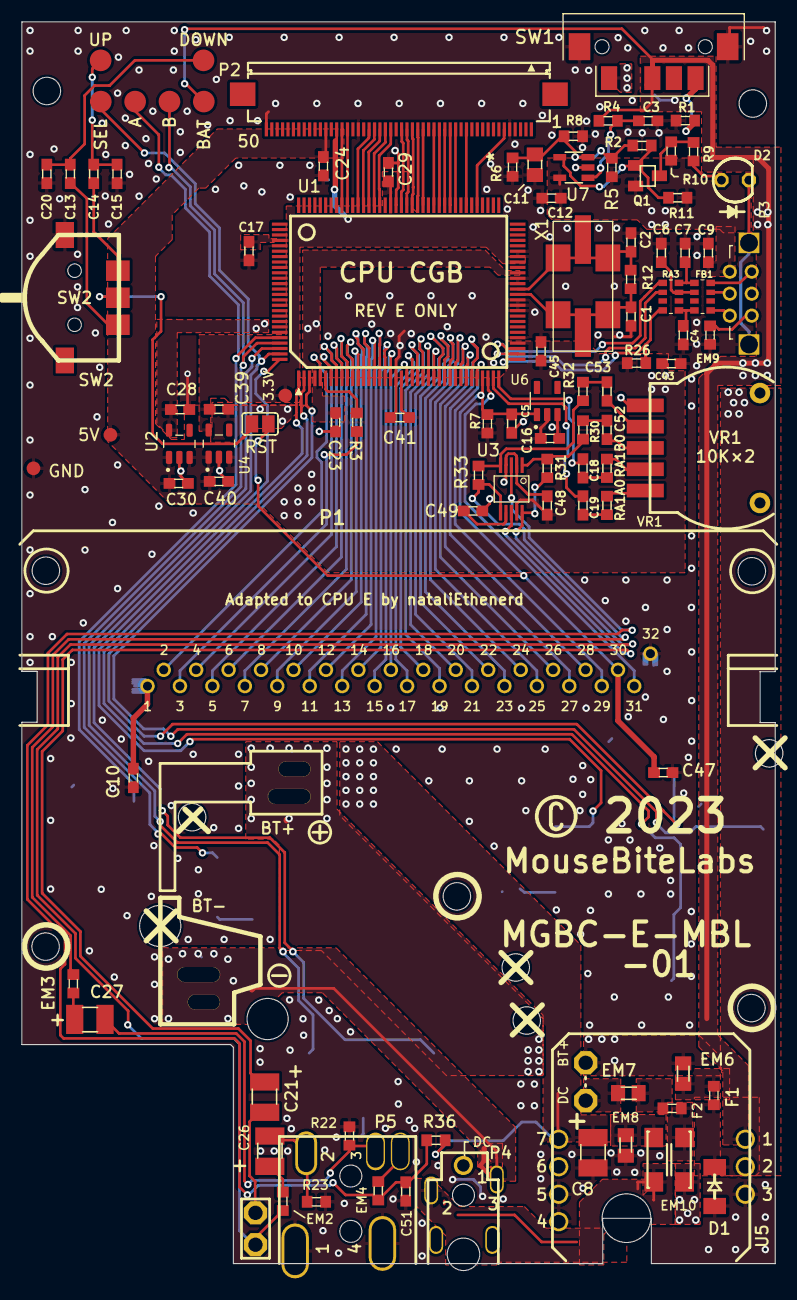
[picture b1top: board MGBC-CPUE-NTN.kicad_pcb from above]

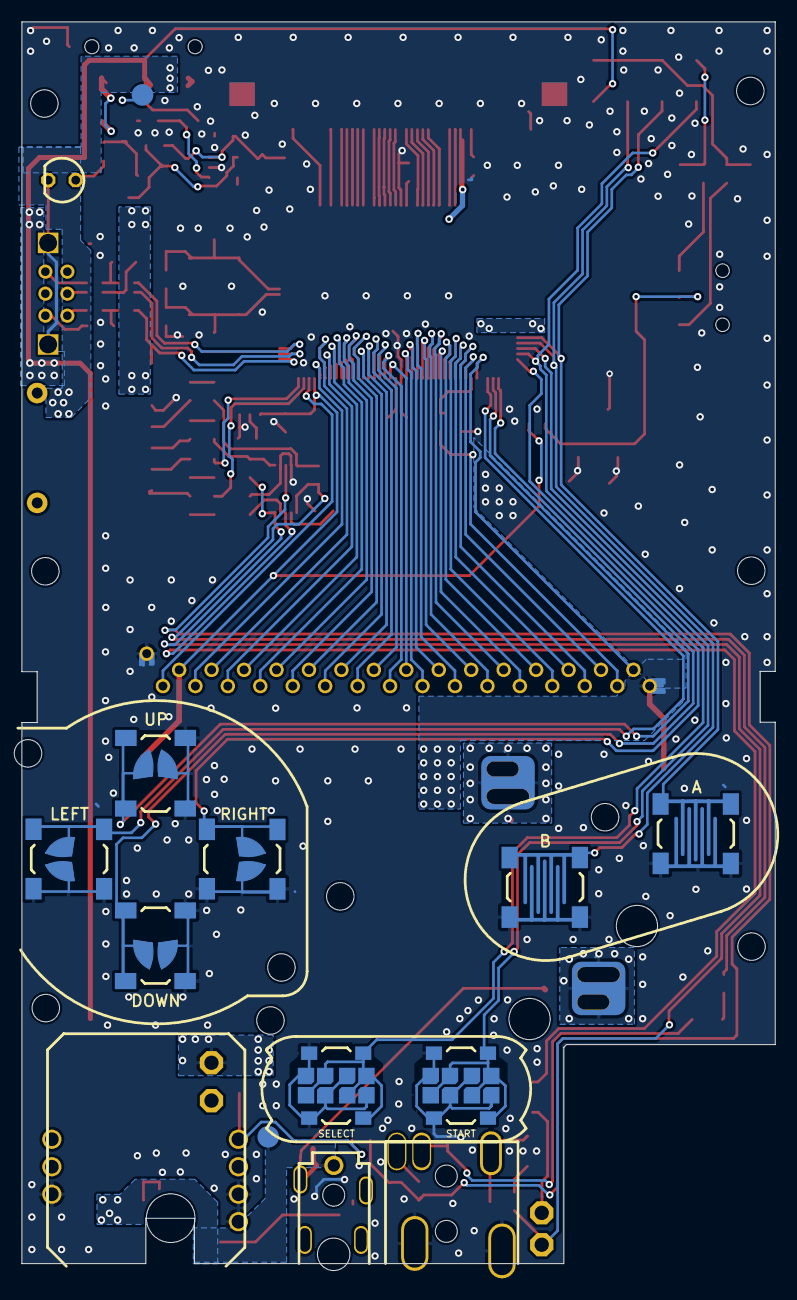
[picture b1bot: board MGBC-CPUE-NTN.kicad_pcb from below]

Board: 2 copper layers, 69.6 x 114.8 mm, 122 parts (11 on the bottom side), 119 nets.

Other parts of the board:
5V: PTR1B1,27; B1,27
@HOLE7, @HOLE8, @HOLE9, @HOLE11: (no value)
GND: PTR1B1,27; B1,27
RST: SJ

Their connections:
+5V: 5V.TP; also elsewhere on the board
/PUSH: RST.2; also elsewhere on the board
/RES: RST.1; also elsewhere on the board
GND: GND.TP; also elsewhere on the board

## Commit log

2024-08-29 kicadfiles
2024-08-30 added gerbers

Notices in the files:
README.md:
License:
This work is licensed under a Creative Commons Attribution-ShareAlike 4.0 International License. You are able to copy and redistribute the material in any medium or format, as well as remix, transform, or build upon the material for any purpose (even commercial) - but you **must** give appropriate credit, provide a link to
©MouseBiteLabs 2023
